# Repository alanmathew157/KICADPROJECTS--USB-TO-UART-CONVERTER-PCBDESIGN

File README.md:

# USB TO UART PCB Design using KICAD -ALTIMUM
## PCB TOP VIEW

## PCB BOTTOM VIEW

## Project Overview🔧
The USB-C to UART converter circuit works by translating USB communication from a computer into UART serial signals that can be used by microcontrollers or other embedded devices. The USB-C connector acts as the input interface, providing 5 V power (VBUS), ground, and the differential data lines D+ and D−. Configuration resistors connected to the CC1 and CC2 pins signal to the host that the device is a USB peripheral, allowing proper USB-C connection and power delivery. The D+ and D− lines are routed to a USB-to-UART bridge IC, which is the core component of the circuit. This IC handles the USB protocol from the computer and internally converts it into UART communication signals, namely TX (transmit) and RX (receive). These UART pins are then connected to the target device, such as a microcontroller, enabling serial data exchange. Supporting components like decoupling capacitors are placed near the IC’s power pins to filter noise and maintain a stable voltage supply, while small resistors may be used for signal conditioning and protection. When the converter is connected to a computer, the system recognizes it as a virtual COM port, allowing communication through serial terminal software. Designing this circuit helped me understand USB-C interface requirements, signal routing, and practical implementation of serial communication while learning PCB design using the KiCad.

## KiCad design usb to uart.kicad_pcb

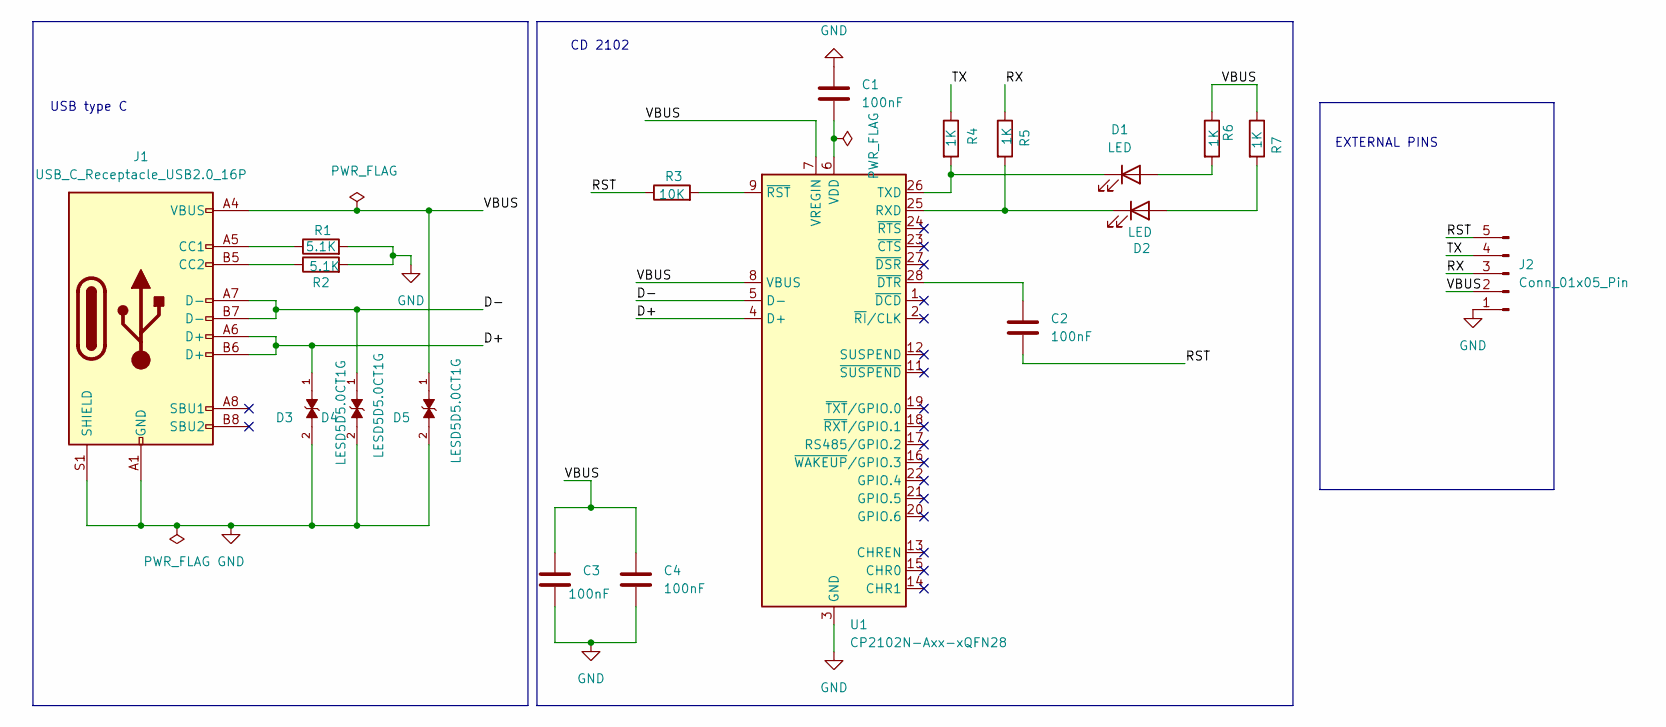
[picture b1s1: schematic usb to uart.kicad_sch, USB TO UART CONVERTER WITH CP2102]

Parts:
C1, C2, C3, C4: 100nF; C_0201_0603Metric
D1, D2: LED; LED_0201_0603Metric
D3, D4, D5: LESD5D5.0CT1G; TVS_LESD5D5.0CT1G; PARTREV O
J1: USB_C_Receptacle_USB2.0_16P; USB_C_Receptacle_HRO_TYPE-C-31-M-12
J2: Conn_01x05_Pin; PinHeader_1x05_P2.54mm_Vertical
R1, R2: 5.1K; R_0201_0603Metric
R3: 10K; R_0201_0603Metric
R4, R5, R6, R7: 1K; R_0201_0603Metric
U1: CP2102N-Axx-xQFN28; QFN-28-1EP_5x5mm_P0.5mm_EP3.35x3.35mm

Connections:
/D+: D3.1, J1.A6 (D+), J1.B6 (D+), U1.4 (D+)
/D-: D4.1, J1.A7 (D-), J1.B7 (D-), U1.5 (D-)
/RST: C2.2, J2.5, R3.1
/RX: J2.3, R5.1
/TX: J2.4, R4.1
/VBUS: C3.1, C4.1, D5.1, J1.A4 (VBUS), J1.A9 (VBUS), J1.B4 (VBUS), J1.B9 (VBUS), J2.2, R6.1, R7.1, U1.7 (VREGIN), U1.8 (VBUS)
GND: C1.1, C3.2, C4.2, D3.2, D4.2, D5.2, J1.A1 (GND), J1.A12 (GND), J1.B1 (GND), J1.B12 (GND), J1.S1 (SHIELD), J2.1, R1.2, R2.2, U1.3 (GND), U1.29 (GND)
unnamed: D1.2 (A), R6.2
unnamed: D1.1 (K), R4.2, U1.26 (TXD)
unnamed: D2.2 (A), R7.2
unnamed: D2.1 (K), R5.2, U1.25 (RXD)
unnamed: J1.A5 (CC1), R1.1
unnamed: J1.B5 (CC2), R2.1
unnamed: C1.2, U1.6 (VDD)
unnamed: C2.1, U1.28 (~DTR)
unnamed: R3.2, U1.9 (~RST)

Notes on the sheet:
CD 2102
EXTERNAL PINS
USB type C

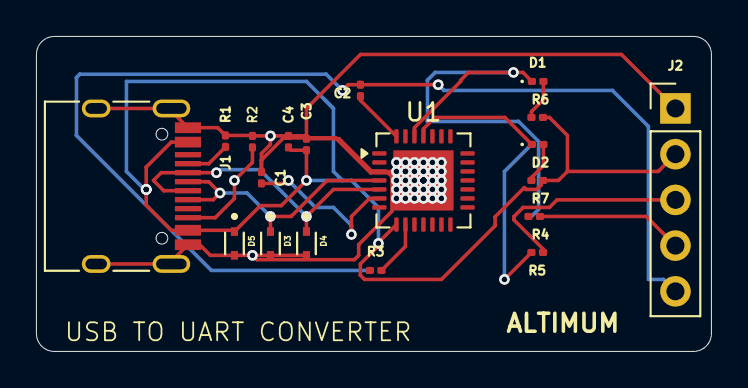
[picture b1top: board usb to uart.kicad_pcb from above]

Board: 2 copper layers, 37.5 x 17.5 mm, 19 parts (0 on the bottom side), 16 nets.
